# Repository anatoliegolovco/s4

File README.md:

# s4 — Sintez 4

**Sintez 2 — Modern Reconstruction & LLM-Driven Visual Simulation.**

A modern, sourceable recreation of the Soviet/Moldovan discrete-TTL ZX Spectrum
clone (keeping a real Zilog Z80), a visual open-source simulator (SimulIDE) the
owner can watch, and a text-only LLM control plane that drives the full
iterate→simulate→verify→layout loop with zero clicks. KiCad is the source of
truth for the PCB.

## Start here

- **Technical spec (canonical):** [`docs/spec/sintez2-recon-spec.md`](./docs/spec/sintez2-recon-spec.md)
- **Docs index:** [`docs/README.md`](./docs/README.md)
- **Decisions:** [`docs/decisions/`](./docs/decisions/)
- **Discussion ledger:** [`docs/ledger/README.md`](./docs/ledger/README.md)
- **Repo layout:** [`docs/repo-layout.md`](./docs/repo-layout.md)

## Source tree

`schematics/` · `kicad/` · `bridge/` · `sim/` · `llm/` · `cpu/` · `tests/` ·
`parts_map.json` — all currently skeletons, populated per milestones T0–T9 in
the spec. All Markdown lives under `docs/` (project rule).

## License

**Proprietary and confidential — © 2026 Lightcypher SRL. All rights reserved.**
This is **not** open-source software. See [`LICENSE`](./LICENSE). Third-party
tools (KiCad, SimulIDE, ngspice, SKiDL) keep their own licenses; mirrored
datasheets/scans under `reference/` belong to their respective owners.

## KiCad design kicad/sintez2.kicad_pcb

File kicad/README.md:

# kicad — canonical project (source of truth for the PCB)

See `docs/spec/sintez2-recon-spec.md` §5.1 and milestones T2/T8.
Gerbers ordered from here. The LLM mostly edits `.kicad_sch` as text and uses
`kicad-cli` for ERC/DRC/netlist/Gerber export (IPC API is PCB-only in 9.0).

(Skeleton — no project authored yet.)

## T8 — PCB (in progress)

The PCB is seeded from the SKiDL netlist (no hand layout):
```bash
# 1. netlist -> board with all footprints (run once to seed)
PYTHONPATH=/usr/lib/python3/dist-packages KICAD9_FOOTPRINT_DIR=/usr/share/kicad/footprints \
  .venv/bin/kinet2pcb -i kicad/sintez2.net -o kicad/sintez2.kicad_pcb -w
# 2. spread footprints + add board outline
PYTHONPATH=/usr/lib/python3/dist-packages python3 kicad/place_board.py
# 3. fab outputs
kicad-cli pcb export gerbers -o kicad/gerbers/ kicad/sintez2.kicad_pcb
kicad-cli pcb export drill   -o kicad/gerbers/ kicad/sintez2.kicad_pcb
```
**Status:** `kicad/sintez2.kicad_pcb` has all 85 footprints placed on a 9×10 grid
(337×320 mm) with an Edge.Cuts outline; Gerber + drill export verified (26 files).
DRC: 23 courtyard/silk overlaps + 421 unconnected pads = **not routed yet**.
**Next:** tighten placement by block; route (manual or Freerouting .dsn/.ses);
then DRC-clean + final Gerbers/BOM. `kicad/sintez2.kicad_pcb` is the layout source
of truth — do NOT re-run kinet2pcb once routing starts (it overwrites the board).

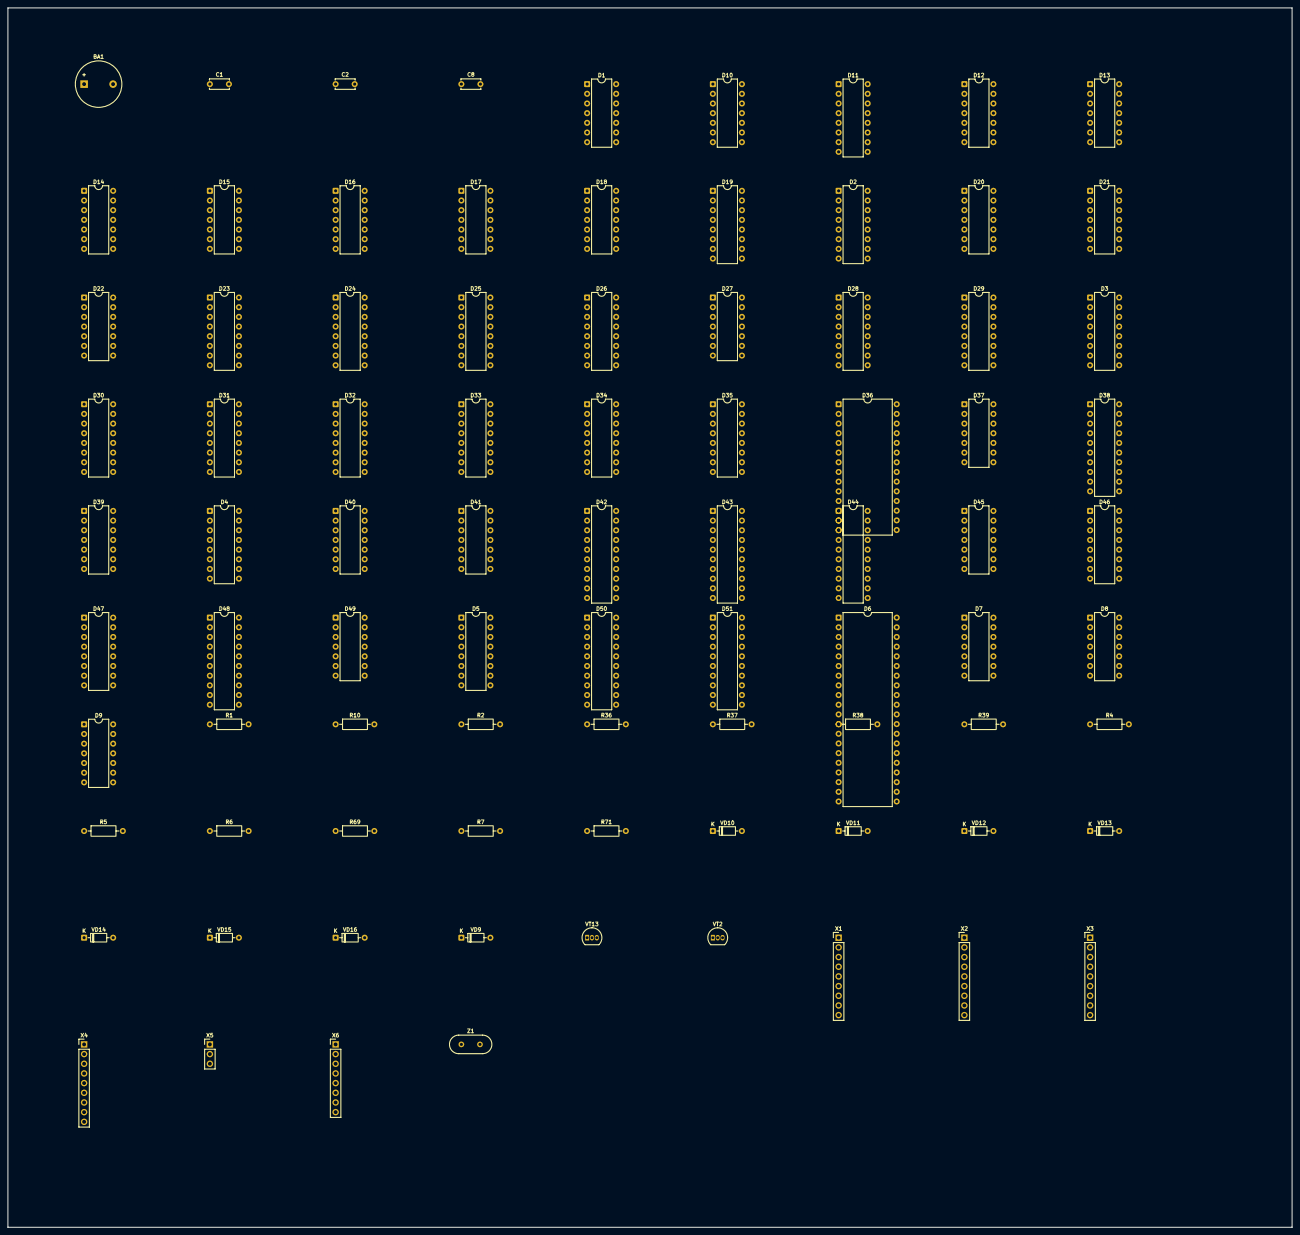
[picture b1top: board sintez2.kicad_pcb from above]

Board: 2 copper layers, 337.0 x 320.0 mm, 85 parts (0 on the bottom side), 141 nets, no tracks yet.

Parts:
BA1: ЗП-3; Buzzer_12x9.5RM7.6
C1: 330p; C_Disc_D5.0mm_W2.5mm_P5.00mm
C2: 10u; C_Disc_D5.0mm_W2.5mm_P5.00mm
C8: 0.022u; C_Disc_D5.0mm_W2.5mm_P5.00mm
D1, D9, D15, D16: К1533ЛН1 (74LS04); DIP-14_W7.62mm
D2, D3, D4, D19: К1533ИЕ7 (74193); DIP-16_W7.62mm
D5: К1533КП11 (74LS257); DIP-16_W7.62mm
D6: КР1858ВМ1/Z84C00; DIP-40_W15.24mm
D7, D13: К1533ЛИ1 (74LS08); DIP-14_W7.62mm
D8, D12, D20, D21: К1533ТМ2 (74LS74); DIP-14_W7.62mm
D10, D27, D37: К1533ЛА4 (74ALS10); DIP-14_W7.62mm
D11: К561ИЕ10 (CD4520); DIP-16_W7.62mm
D14, D22: К1533ЛЕ1 (74LS02); DIP-14_W7.62mm
D17: К1533ЛА3 (74ALS00); DIP-14_W7.62mm
D18: К1533ЛП5 (74LS86); DIP-14_W7.62mm
D23, D24, D25, D26, D46, D47: К1533КП12 (74ALS253); DIP-16_W7.62mm
D28, D29, D30, D31, D32, D33, D34, D35: К565РУ5 (4164); DIP-16_W7.62mm
D36: 27128 (ПЗУ); DIP-28_W15.24mm
D38: КР1533ИР27 (74273); DIP-20_W7.62mm
D39, D40, D41, D45: К555ИР16 (4-bit shift, keep LS); DIP-14_W7.62mm
D42: К1533ИР23 (74LS374); DIP-20_W7.62mm
D43, D44, D48, D51: К1533ИР22 (74LS373); DIP-20_W7.62mm
D49: К544СА3 (comparator); DIP-14_W7.62mm
D50: К1533АП3 (74LS244); DIP-20_W7.62mm
R1, R2: 470; R_Axial_DIN0207_L6.3mm_D2.5mm_P10.16mm_Horizontal
R4, R5, R6, R7, R10, R36, R39: 5.1k; R_Axial_DIN0207_L6.3mm_D2.5mm_P10.16mm_Horizontal
R37: 1.8M; R_Axial_DIN0207_L6.3mm_D2.5mm_P10.16mm_Horizontal
R38: 3k; R_Axial_DIN0207_L6.3mm_D2.5mm_P10.16mm_Horizontal
R69: 33k; R_Axial_DIN0207_L6.3mm_D2.5mm_P10.16mm_Horizontal
R71: 820; R_Axial_DIN0207_L6.3mm_D2.5mm_P10.16mm_Horizontal
VD9, VD10, VD11, VD12, VD13, VD14, VD15, VD16: КД522; D_DO-35_SOD27_P7.62mm_Horizontal
VT2, VT13: КТ315; TO-92_Inline
X1: JoyL; PinHeader_1x09_P2.54mm_Vertical
X2: JoyR; PinHeader_1x09_P2.54mm_Vertical
X3: Kbd; PinHeader_1x09_P2.54mm_Vertical
X4: DiskDO; PinHeader_1x09_P2.54mm_Vertical
X5: Tape; PinHeader_1x03_P2.54mm_Vertical
X6: DiskAA; PinHeader_1x08_P2.54mm_Vertical
Z1: 14MHz; Crystal_HC49-U_Vertical

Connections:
+5V: D1.14, D2.16, D3.16, D4.16, D5.16, D6.11, D7.14, D8.1, D8.4, D8.10, D8.13, D8.14, D9.14, D10.14, D11.16, D12.14, D13.14, D14.14, D15.14, D16.14, D17.14, D18.14, D19.16, D20.14, D21.14, D22.14, D23.16, D24.16, D25.16, D26.16, D27.14, D28.8, D29.8, D30.8, D31.8, D32.8, D33.8, D34.8, D35.8, D36.1, D36.27, D36.28, D37.14, D38.20, D39.14, D40.14, D41.14, D42.20, D43.20, D44.20, D45.14, D46.16, D47.16, D48.20, D49.2, D49.11, D50.20, D51.20, R4.1, R5.1, R6.1, R7.1, R10.1, R36.1, R38.2, R71.1
A0: D6.30, D23.6, D36.10, R39.1
A1: D6.31, D23.10, D36.9
A2: D6.32, D24.6, D36.8
A3: D6.33, D24.10, D36.7
A4: D6.34, D25.6, D36.6
A5: D6.35, D23.11, D36.5
A6: D6.36, D24.5, D36.4
A7: D6.37, D24.11, D36.3
A8: D6.38, D25.10, D36.25, D50.2
A9: D6.39, D26.6, D36.24, D50.4
A10: D6.40, D23.5, D36.21, D50.6
A11: D6.1, D25.5, D36.23, D50.8
A12: D6.2, D25.11, D36.2, D50.13
A13: D6.3, D26.5, D36.26, D50.11
A14: D6.4, D22.2, D26.10, D50.17
A15: D6.5, D22.3, D26.11, D50.15
AA8: VD9.2, X6.6
AA9: VD10.2, X6.3
AA10: VD11.2, X6.2
AA11: VD12.2, X1.7, X6.1
AA12: VD15.2, X2.7, X6.4
AA13: VD16.2, X6.5
AA14: VD13.2, X6.7
AA15: VD14.2, X6.8
ARB_OE0: D23.1, D24.1, D25.1, D26.1
ARB_SELA: D23.14, D24.14, D25.14, D26.14
ARB_SELB: D23.2, D24.2, D25.2, D26.2
B0: D42.2, D46.5
B1: D42.9, D46.6
BB: D46.3, D46.4, D48.2
BM: D45.2, D46.7
BORDER: D46.2, D47.2
CLK: D6.6, D8.9
CLK7: D2.5, D8.5, D8.11
CLK14: D1.4, D8.3, D39.9, D40.9, D41.9, D45.9, R2.2
D0: D6.14, D28.2, D36.11, D43.2, D44.2, D48.3, D51.2
D1: D6.15, D29.2, D36.12, D43.5, D44.5, D48.4, D51.5
D2: D6.12, D30.2, D36.13, D43.6, D44.6, D48.7, D51.6
D3: D6.8, D31.2, D36.15, D43.9, D44.9, D48.13, D51.9
D4: D6.7, D32.2, D36.16, D43.12, D44.12, D48.8, D51.12
D5: D6.9, D33.2, D36.17, D43.15, D44.15, D51.15
D6: D6.10, D34.2, D36.18, D43.16, D44.16, D51.16
D7: D6.13, D35.2, D36.19, D43.19, D44.19, D51.19
D49_QK: D49.9, R37.2, R38.1, R39.2
D50_OE: D50.1, D50.19
DO0: X1.3, X2.9, X4.4
DO1: X1.2, X2.5, X4.5
DO2: X1.4, X2.4, X4.6
DO3: X1.5, X2.2, X4.7
DO4: X1.9, X2.3, X4.8
G0: D42.6, D47.5
G1: D42.15, D47.6
GB: D47.3, D47.4, D48.6
GM: D45.4, D47.7
GND: C1.2, C2.2, D1.7, D2.8, D3.8, D4.8, D5.8, D5.15, D6.29, D7.7, D8.7, D9.7, D10.7, D11.8, D12.7, D13.7, D14.7, D15.7, D16.7, D17.7, D18.7, D19.8, D20.7, D21.7, D22.7, D23.8, D23.15, D24.8, D24.15, D25.8, D25.15, D26.3, D26.8, D26.13, D26.15, D27.7, D28.16, D29.16, D30.16, D31.16, D32.16, D33.16, D34.16, D35.16, D36.14, D37.7, D38.1, D38.10, D39.6, D39.7, D39.8, D40.6, D40.7, D40.8, D41.1, D41.6, D41.7, D41.8, D42.1, D42.10, D43.10, D44.1, D44.10, D44.11, D44.14, D44.17, D44.18, D45.1, D45.7, D45.8, D46.8, D46.15, D47.8, D47.15, D48.1, D48.10, D49.6, D50.10, D51.10, D51.11, D51.14, D51.18, VT2.1, VT13.1, X5.2
H1: D2.3, D23.12
H2: D2.2, D24.4
H3: D2.6, D24.12
H4: D2.7, D25.4
J0: D44.3, X3.2
J1: D44.4, X3.3
J2: D44.7, X3.4
J3: D44.8, X3.5
J4: D44.13, X3.9
K8: D5.12, D25.12
K9: D5.9, D26.4
K10: D7.6, D23.3
K11: D5.7, D25.3
K12: D5.4, D25.13
MEM_STB: D13.4, D13.9
MREQ_H: D9.2, D17.2
unnamed: D8.2, D8.6
unnamed: D8.8, D8.12
unnamed: D2.12, D19.5
unnamed: D3.5, D19.12
unnamed: D3.12, D4.5
unnamed: D40.1, D41.10
unnamed: D13.12, D39.1, D40.10
unnamed: C8.2, D49.4, R36.2, R37.1
OSC_IN: C1.1, D1.1, R1.1, Z1.1
OSC_MID: D1.2, D1.3, R1.2, R2.1, Z1.2
PIX_SER: D18.9, D39.10
R0: D42.5, D46.11
R1: D42.12, D46.10
RB: D46.12, D46.13, D48.5
RM: D45.3, D46.9
ROM_REGION: D17.1, D22.1
SPK_VT2_COLL: BA1.2, R69.1, VT2.3
TAPE_IN: C8.1, X5.3
V0: D3.3, D5.13
V1: D3.2, D5.10
V2: D3.6, D7.5
V3: D3.7, D23.13
V4: D4.3, D24.3
V5: D4.2, D24.13
V6: D4.6, D5.6, D5.14
V7: D4.7, D5.3, D5.11
VA0: D23.7, D28.5, D29.5, D30.5, D31.5, D32.5, D33.5, D34.5, D35.5
VA1: D23.9, D28.7, D29.7, D30.7, D31.7, D32.7, D33.7, D34.7, D35.7
VA2: D24.7, D28.6, D29.6, D30.6, D31.6, D32.6, D33.6, D34.6, D35.6
VA3: D24.9, D28.12, D29.12, D30.12, D31.12, D32.12, D33.12, D34.12, D35.12
VA4: D25.7, D28.11, D29.11, D30.11, D31.11, D32.11, D33.11, D34.11, D35.11
VA5: D25.9, D28.10, D29.10, D30.10, D31.10, D32.10, D33.10, D34.10, D35.10
VA6: D26.7, D28.13, D29.13, D30.13, D31.13, D32.13, D33.13, D34.13, D35.13
VA7: D26.9, D28.9, D29.9, D30.9, D31.9, D32.9, D33.9, D34.9, D35.9
VD0: D41.2, D42.3, D43.3
VD1: D41.3, D42.4, D43.4
VD2: D41.4, D42.7, D43.7
VD3: D41.5, D42.8, D43.8
VD4: D40.2, D42.13, D43.13
VD5: D40.3, D42.14, D43.14
VD6: D40.4, D42.17, D43.17
VD7: D40.5, D42.18, D43.18
VID_OE: D46.1, D47.1
VID_SEL: D46.14, D47.14
VT13_BASE: BA1.1, R69.2, VT13.2
VT13_COLL: R71.2, VT13.3
Y: D42.16, D47.10, D47.11
YM: D45.5, D47.9
a2: D5.2, D5.5, D26.12
dA8: D50.18, VD9.1
dA9: D50.16, VD10.1
dA10: D50.14, VD11.1
dA11: D50.12, VD12.1
dA12: D50.7, VD15.1
dA13: D50.9, VD16.1
dA14: D50.3, VD13.1
dA15: D50.5, VD14.1
nS2: D5.1, D7.4
~BUSRQ: D6.25, R6.2
~CAS: D13.8, D28.15, D29.15, D30.15, D31.15, D32.15, D33.15, D34.15, D35.15
~INT: D6.16, R4.2
~MREQ: D6.19, D9.1
~NMI: D6.17, R5.2
~RAS: D13.6, D28.4, D29.4, D30.4, D31.4, D32.4, D33.4, D34.4, D35.4
~RESET: C2.1, D6.26, R10.2
~ROMCS: D17.3, D36.20
~ROMOE: D6.21, D36.22
~WAIT: D6.24, R7.2
~WR: D6.22, D28.3, D29.3, D30.3, D31.3, D32.3, D33.3, D34.3, D35.3

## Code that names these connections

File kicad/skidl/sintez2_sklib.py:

from collections import defaultdict
from skidl import Pin, Part, Alias, SchLib, SKIDL, TEMPLATE

from skidl.pin import pin_types

SKIDL_lib_version = '0.0.1'

sintez2 = SchLib(tool=SKIDL).add_parts(*[
        Part(**{ 'name':'Z84C00', 'dest':TEMPLATE, 'tool':SKIDL, 'aliases':Alias({'Z84C00'}), 'ref_prefix':'D', 'fplist':None, 'footprint':'Package_DIP:DIP-40_W15.24mm', 'keywords':None, 'description':'', 'datasheet':None, 'pins':[
            Pin(num='1',name='A11',func=pin_types.OUTPUT),
            Pin(num='2',name='A12',func=pin_types.OUTPUT),
            Pin(num='3',name='A13',func=pin_types.OUTPUT),
            Pin(num='4',name='A14',func=pin_types.OUTPUT),
            Pin(num='5',name='A15',func=pin_types.OUTPUT),
            Pin(num='6',name='CLK',func=pin_types.INPUT),
            Pin(num='7',name='D4',func=pin_types.BIDIR),
            Pin(num='8',name='D3',func=pin_types.BIDIR),
            Pin(num='9',name='D5',func=pin_types.BIDIR),
            Pin(num='10',name='D6',func=pin_types.BIDIR),
            Pin(num='11',name='VCC',func=pin_types.PWRIN),
            Pin(num='12',name='D2',func=pin_types.BIDIR),
            Pin(num='13',name='D7',func=pin_types.BIDIR),
            Pin(num='14',name='D0',func=pin_types.BIDIR),
            Pin(num='15',name='D1',func=pin_types.BIDIR),
            Pin(num='16',name='~INT',func=pin_types.INPUT),
            Pin(num='17',name='~NMI',func=pin_types.INPUT),
            Pin(num='18',name='~HALT',func=pin_types.OUTPUT),
            Pin(num='19',name='~MREQ',func=pin_types.TRISTATE),
            Pin(num='20',name='~IORQ',func=pin_types.TRISTATE),
            Pin(num='21',name='~RD',func=pin_types.TRISTATE),
            Pin(num='22',name='~WR',func=pin_types.TRISTATE),
            Pin(num='23',name='~BUSAK',func=pin_types.OUTPUT),
            Pin(num='24',name='~WAIT',func=pin_types.INPUT),
            Pin(num='25',name='~BUSRQ',func=pin_types.INPUT),
            Pin(num='26',name='~RESET',func=pin_types.INPUT),
            Pin(num='27',name='~M1',func=pin_types.OUTPUT),
            Pin(num='28',name='~RFSH',func=pin_types.OUTPUT),
            Pin(num='29',name='GND',func=pin_types.PWRIN),
            Pin(num='30',name='A0',func=pin_types.TRISTATE),
            Pin(num='31',name='A1',func=pin_types.TRISTATE),
            Pin(num='32',name='A2',func=pin_types.TRISTATE),
            Pin(num='33',name='A3',func=pin_types.TRISTATE),
            Pin(num='34',name='A4',func=pin_types.TRISTATE),
            Pin(num='35',name='A5',func=pin_types.TRISTATE),
            Pin(num='36',name='A6',func=pin_types.TRISTATE),
            Pin(num='37',name='A7',func=pin_types.TRISTATE),
            Pin(num='38',name='A8',func=pin_types.TRISTATE),
            Pin(num='39',name='A9',func=pin_types.TRISTATE),
            Pin(num='40',name='A10',func=pin_types.TRISTATE)] }),
        Part(**{ 'name':'Crystal', 'dest':TEMPLATE, 'tool':SKIDL, 'aliases':Alias({'Crystal'}), 'ref_prefix':'Z', 'fplist':None, 'footprint':'Crystal:Crystal_HC49-U_Vertical', 'keywords':None, 'description':'', 'datasheet':None, 'pins':[
            Pin(num='1',name='1',func=pin_types.PASSIVE),
            Pin(num='2',name='2',func=pin_types.PASSIVE)] }),
        Part(**{ 'name':'K1533LN1', 'dest':TEMPLATE, 'tool':SKIDL, 'aliases':Alias({'K1533LN1'}), 'ref_prefix':'D', 'fplist':None, 'footprint':'Package_DIP:DIP-14_W7.62mm', 'keywords':None, 'description':'', 'datasheet':None, 'pins':[
            Pin(num='1',name='1A',func=pin_types.INPUT),
            Pin(num='2',name='1Y',func=pin_types.OUTPUT),
            Pin(num='3',name='2A',func=pin_types.INPUT),
            Pin(num='4',name='2Y',func=pin_types.OUTPUT),
            Pin(num='5',name='3A',func=pin_types.INPUT),
            Pin(num='6',name='3Y',func=pin_types.OUTPUT),
            Pin(num='7',name='GND',func=pin_types.PWRIN),
            Pin(num='8',name='4Y',func=pin_types.OUTPUT),
            Pin(num='9',name='4A',func=pin_types.INPUT),
            Pin(num='10',name='5Y',func=pin_types.OUTPUT),
            Pin(num='11',name='5A',func=pin_types.INPUT),
            Pin(num='12',name='6Y',func=pin_types.OUTPUT),
            Pin(num='13',name='6A',func=pin_types.INPUT),
            Pin(num='14',name='VCC',func=pin_types.PWRIN)] }),
        Part(**{ 'name':'R', 'dest':TEMPLATE, 'tool':SKIDL, 'aliases':Alias({'R'}), 'ref_prefix':'R', 'fplist':None, 'footprint':'Resistor_THT:R_Axial_DIN0207_L6.3mm_D2.5mm_P10.16mm_Horizontal', 'keywords':None, 'description':'', 'datasheet':None, 'pins':[
            Pin(num='1',name='~',func=pin_types.PASSIVE),
            Pin(num='2',name='~',func=pin_types.PASSIVE)] }),
        Part(**{ 'name':'C', 'dest':TEMPLATE, 'tool':SKIDL, 'aliases':Alias({'C'}), 'ref_prefix':'C', 'fplist':None, 'footprint':'Capacitor_THT:C_Disc_D5.0mm_W2.5mm_P5.00mm', 'keywords':None, 'description':'', 'datasheet':None, 'pins':[
            Pin(num='1',name='~',func=pin_types.PASSIVE),
            Pin(num='2',name='~',func=pin_types.PASSIVE)] })])

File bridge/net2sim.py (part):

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        items.append(f'<item itemtype="Memory" CircId="{cid}" {A} Pos="900,-360" label="D36 ROM(27128)" Address_Bits="14 _Bits" Data_Bits="8 _Bits" Persistent="true" Asynch="true"{memattr} {ELEC} />')
        for i in range(14): mem_attach("ROM", cid, f"in{i}",  f"in{i}",  f"A{i}", 900, -360 + i*8)
        for i in range(8):  mem_attach("ROM", cid, f"out{i}", f"out{i}", f"D{i}", 990, -360 + i*8)
        mem_attach("ROM", cid, "cs", "Pin_Cs",        "~ROMCS", 900, -392)
        mem_attach("ROM", cid, "oe", "Pin_outEnable", "~ROMOE", 900, -384)
        warns.append("D36 -> one Memory(16Kx8)")
    if "K565RU5" in present:
        uid += 1; cid = f"DynamicMemory-{uid}"
        items.append(f'<item itemtype="DynamicMemory" CircId="{cid}" {A} Pos="900,-120" label="DRAM 64Kx8(D28-35)" Row_Bits="8 _Bits" Column_Bits="8 _Bits" Data_Bits="8 _Bits" {ELEC} />')
        for i in range(8): mem_attach("DRAM", cid, f"in{i}",  f"in{i}",  f"VA{i}", 900, -120 + i*8)
        for i in range(8): mem_attach("DRAM", cid, f"out{i}", f"out{i}", f"D{i}", 990, -120 + i*8)
        mem_attach("DRAM", cid, "ras", "Pin_Ras", "~RAS", 900, -150)
        mem_attach("DRAM", cid, "cas", "Pin_Cas", "~CAS", 900, -142)
        mem_attach("DRAM", cid, "we",  "Pin_We",  "~WR",  900, -134)
        warns.append("D28-D35 -> one DynamicMemory(64Kx8); data out0-7 on the D bus (DD->D43 path not modeled)")
    nets = [(nm, eps) for nm, eps in netmap.items()]
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
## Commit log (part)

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2026-06-13 Add docs structure with discussion ledger, templates, and rules
2026-06-13 Inaugurate Sintez 2 project: spec, decisions, ledger, repo skeleton
    - Register canonical tech spec at docs/spec/sintez2-recon-spec.md
    - Record four non-negotiable constraints as decision records (0001-0004)
    - Seed discussion ledger: inception, architecture, tooling, sourcing topics
    with the project charter (resolved) and open questions
    - Lay down spec §9 repo skeleton (schematics, kicad, bridge, sim, llm, cpu,
    tests) with placeholder READMEs
2026-06-13 Add reference materials, datasheets, and T1 schematic findings
    - Save owner-supplied primary sources under reference/ (committed):
    Sintez-2 mainboard schematic (scan + redraw), Beta Disk board photo,
    128KB expansion writeup, SCART/Jack video pinout
    - Catalog them with provenance in docs/references/sources-catalog.md
    - Collect datasheets + key parameters in docs/datasheets/README.md
    - parts_map.json v1: confirm К1533ИЕ7=74ALS193, КП12=74ALS253,
2026-06-13 Extract mainboard BOM + wiring from schematic (tiles kept)
    - Segment the mainboard schematic into a 3x4 350-dpi grid; keep tiles in
    schematics/tiles/ (committed) with a grid map README
    - schematics/bom.json: ~40 packages identified with confidence flags —
    D6=Z80 (power pins 11/29), D28-D35=К565РУ5 DRAM, D36=16KB ROM,
    D39/D40/D61=ИР16 pixel chain, D23-D26=КП12 arbitration, D2/D3/D4/D19=ИЕ7
    - schematics/wiring.json: buses, control signals, connector pinouts, power
2026-06-13 Tile + extract the colorized vector redraw (net names, K1533 family)
    - Tile reference/schematics/sintez2-original.pdf (vector redraw) into a 4x3
    grid in schematics/tiles-color/, plus per-color layer separations
    (parts=dark-red, net-labels=blue, wires=other colors) and high-zoom crops
    - Decode color semantics; redraw names nets + prints exact part numbers, so it
    is now the primary net source (scan is the cross-check)
    - BOM/wiring -> v0.2 corrections: family K1533 (registers K555IR16/22/23, DRAM
2026-06-13 Record Russian-forum corroboration for the Sintez-2 BOM gaps
    - Web-searched zx-pk.ru (t-240), Habr, Pikabu: no per-designator BOM/netlist is
    published; our schematic (from ZX-Club #7) is authoritative. Forums confirm
    only top-level specs.
    - Concrete gains: 128K mod lifts 3 pins of the КП12 A14/A15 mux + 2nd РУ5 row
    with CAS split -> corroborates D26 КП12 as the A14/A15 paging mux
    - D36 ROM = 28-pin 16Kx8 EPROM (27128-class; К573РФ6/РФ8 or imported)
2026-06-13 Resolve most BOM gaps from color tiles (IA unreachable)
    - Internet Archive (web.archive.org) and archive.ph are blocked by this
    environment's egress policy; forum mirrors are dead. Recorded as such.
    - Pivoted to high-zoom color-tile crops (no board/internet needed):
    D5=КП12 (video-addr K8-K12 from V-counters), D11=К561ИЕ10/CD4520 (resolves
    ИЕ10), D26=КП12, D36=27128 (labeled literally), D48=ИР22 (border BB/RB/GB)
    - Captured К565РУ5 address-pin -> VADDR map and K8-K12 video-fetch bus in
2026-06-13 Add Sintez-2 board photos from Russian web (habr, priborazbor)
    - Downloaded motherboard photos (image CDNs reachable; web.archive.org is not):
    reference/photos/sintez2-board-habr.jpg (1920x1278 original) + priborazbor view
    - Confirms CPU = imported Zilog Z8400 (ceramic), layout matches schematic,
    КТ315 output transistors; scrap-content count is a rough total-IC cross-check
    - 1920px too low to read individual silkscreen designators; D37/D44/D49/D50/D51
    still unresolved (need higher-res photo or more color-redraw high-zoom reads)
2026-06-13 Deeper image search: exhaust online board photos, add rear panel
    - Pulled all 8 habr article images at max res; habrastorage caps at 1920px and
    only one is a board shot. Full-res host beta.hstor.org is dead (no DNS).
    - Conclusion: no higher-res Sintez-2 board photo exists online than the 1920px
    habr shot - insufficient for tiny silkscreen designators
    - Saved reference/photos/sintez2-rear-panel.jpg (corroborates connector set:
    PS/TV/RESET + card-edge X8 bus + DB9/DIN; nameplate dates unit 1995)
2026-06-13 Deeper Russian search: repair threads corroborate BOM (no hi-res photo)
    - Russian-targeted queries surfaced Sintez-2 repair threads (zx-pk.ru 27280/
    19568, zx-pk.com 17915). Their photos are 799x599 thumbnails + TV diagnostic
    screens - no readable board close-up. S2_09.jpg = lower-res copy of our sheet
    (confirms page 29, ПРИЛОЖЕНИЕ 2, canonical)
    - Forum text corroborates: D39-D42 = pixel+attribute gen, КР1533КП12 video
    muxes, ИР16; rebuild notes (К555<->К1533, РУ5 В/Г, 27128->W27C512)
2026-06-13 Add owner-supplied YouTube reference + online sources to catalog
    - Save https://youtu.be/0_mFe5sdLsc (Sintez-2 video) to sources-catalog.md
    - Record the web sources used in research (habr, zx-pk repair threads,
    priborazbor) and the egress reachability note
2026-06-13 Fold Muravyev-Drive findings into bom.json/wiring.json (v0.4) + bom.md export
    - bom.json v0.4: add package_inventory (full Питание микросхем table); D6=
    КР1858ВМ1 (14.3MHz/4); resolve D37/D44/D49/D50/D51 (located + pin-count from
    element-placement); flag ir16_pincount_conflict on D39-D41/D45
    - wiring.json v0.4: X7 'TV' pinout high-confidence; X8 = SNP58-64 card-edge note
    - schematics/bom.md: new ReSintez-aligned human-readable BOM (corrects the site's
    generic placeholder: 8x К565РУ5 not '6x 4164', single 27128 not '2716/2732',
2026-06-13 Record execution-visualization decision: in-simulator monitor, mixed-level
    - Owner directive: watch execution INSIDE the electronics simulator (SimulIDE) —
    real components wired, real ROM, custom monitor component rendering RGB+sync in
    a window. NOT a Sintez emulator.
    - New ledger entry tooling/execution-visualization-monitor.md: why full
    gate-level is 100x-10000x slower than real-time (GHz = ops/sec, not '3 MHz';
    billions of gate-events/sec; serial vs parallel; GUI overhead), and the path to
2026-06-14 Gitignore SKiDL build artifacts (.erc/.log/_sklib.py); drop stray files
2026-06-15 net2sim: compact grid layout that fits the canvas (1200x1050)
    Drop the wide single-row+channel router (7920px wide). Components on a compact 7-col
    grid; nets = drawn wires chained via centroid Nodes with direct lines (wire overlap
    is fine per user). Extent ~1200x1050; 0 load errors; 27 items, 48 nodes, 121 wires.
2026-06-15 Fix D5 to К1533КП11 (74257) in SKiDL — matches the validated correction
    D5 is a quad 2:1 mux (КП11/74257), not КП12 (the trace-verify workflow + bom v0.3).
    Its outputs weren't wired yet, so the type change is clean. 0 ERC errors.
2026-06-16 Add KiCad project file (.kicad_pro); gitignore .kicad_prl/.bak
    The .kicad_pro lets the board open directly in the KiCad GUI. Local prefs (.kicad_prl)
    and pcbnew .bak backups are gitignored.
2026-06-16 T8: re-seed PCB from the updated netlist (arbitration wired, 173 nets)
    kinet2pcb re-run after the arbitration/counter wiring; 85 footprints placed (9x10
    grid) + Edge.Cuts outline. DSN re-exported for routing.

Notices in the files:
bridge/net2sim.py:
is the José Leandro Sintez-M dump — verified ZX48 ROM (start DI/XOR A/JP $11CB,
IM1 handler at $0038, © glyph at the tail).
